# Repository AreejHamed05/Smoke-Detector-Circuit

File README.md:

# 🚨 Smoke/Gas Detector Circuit

A compact and affordable smoke/gas detection system using the **MQ-2 gas sensor**, designed for early fire warning. The system was built using **Proteus simulation**, **breadboard prototyping**, and **PCB implementation** for real-world testing.

---

## 🔧 Project Overview

This project detects flammable gases like smoke, methane, and LPG. When gas is detected above a threshold, the system triggers an **LED** and **buzzer** as a dual alert mechanism.

- 📦 Fully simulated using **Proteus** and **Tinkercad**
- ⚡ Implemented on both **breadboard** and **fabricated PCB**
- 🔋 Stable power regulation with **LM7805**

---

## 🧠 My Role

- Designed the full schematic and PCB layout using Proteus
- Simulated and debugged the circuit
- Assembled and calibrated the sensor and components on breadboard and PCB
- Performed real-world testing with and without gas exposure

---

## 🛠️ Tools & Components

- MQ-2 Gas Sensor
- LM7805 Voltage Regulator
- Buzzer, LED, Resistors
- Breadboard & PCB
- Proteus (Simulation)
- Tinkercad (Virtual circuit testing)

---

## ✅ Features

- Real-time gas detection
- Dual alert: visual (LED) and sound (buzzer)
- Compact PCB layout for physical implementation
- Safe and affordable system

---

## 📅 Date

**Fall 2024 – 2025** (University project)

---

## ✍️ Author

**Areej Abdelghany Hamed**  
Mechatronics Engineering Student  
[LinkedIn](https://www.linkedin.com/in/areejhamed) | areejhamed05@gmail.com

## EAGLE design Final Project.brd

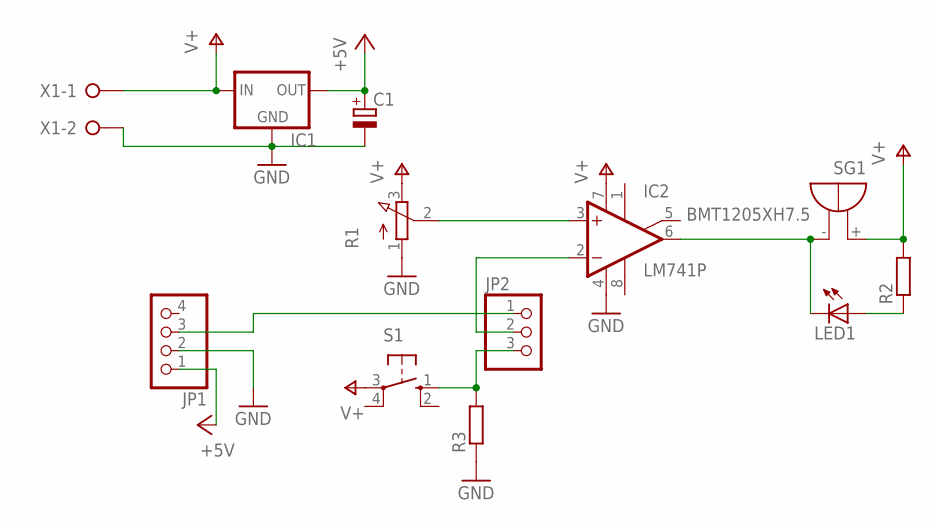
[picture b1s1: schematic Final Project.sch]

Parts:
C1: CPOL-EUE2.5-7; E2,5-7
IC1: 78MXXS
IC2: LM741P; DIL08
JP1: PINHD-1X4; 1X04
JP2: PINHD-1X3; 1X03
LED1: LED5MM
R1: 3RP/1610N
R2, R3: R-EU_0207/7; 0207/7
S1: 10-XX; B3F-10XX
SG1: BMT1205XH7.5
X1: W237-02P; W237-132

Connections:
+5V: C1.+, IC1.OUT, JP1.1
GND: C1.-, IC1.GND, IC2.4 (V-), JP1.2, R1.1 (A), R3.1, X1.2
unnamed: JP2.3, R3.2, S1.1 (S)
unnamed: JP1.3, JP2.1
unnamed: IC2.3 (+IN), R1.2 (S)
unnamed: IC2.6 (OUT), LED1.K (C), SG1.-
unnamed: LED1.A, R2.1
unnamed: IC2.2 (-IN), JP2.2
V+: IC1.IN, IC2.7 (V+), R1.3 (E), R2.2, S1.3, SG1.+, X1.1

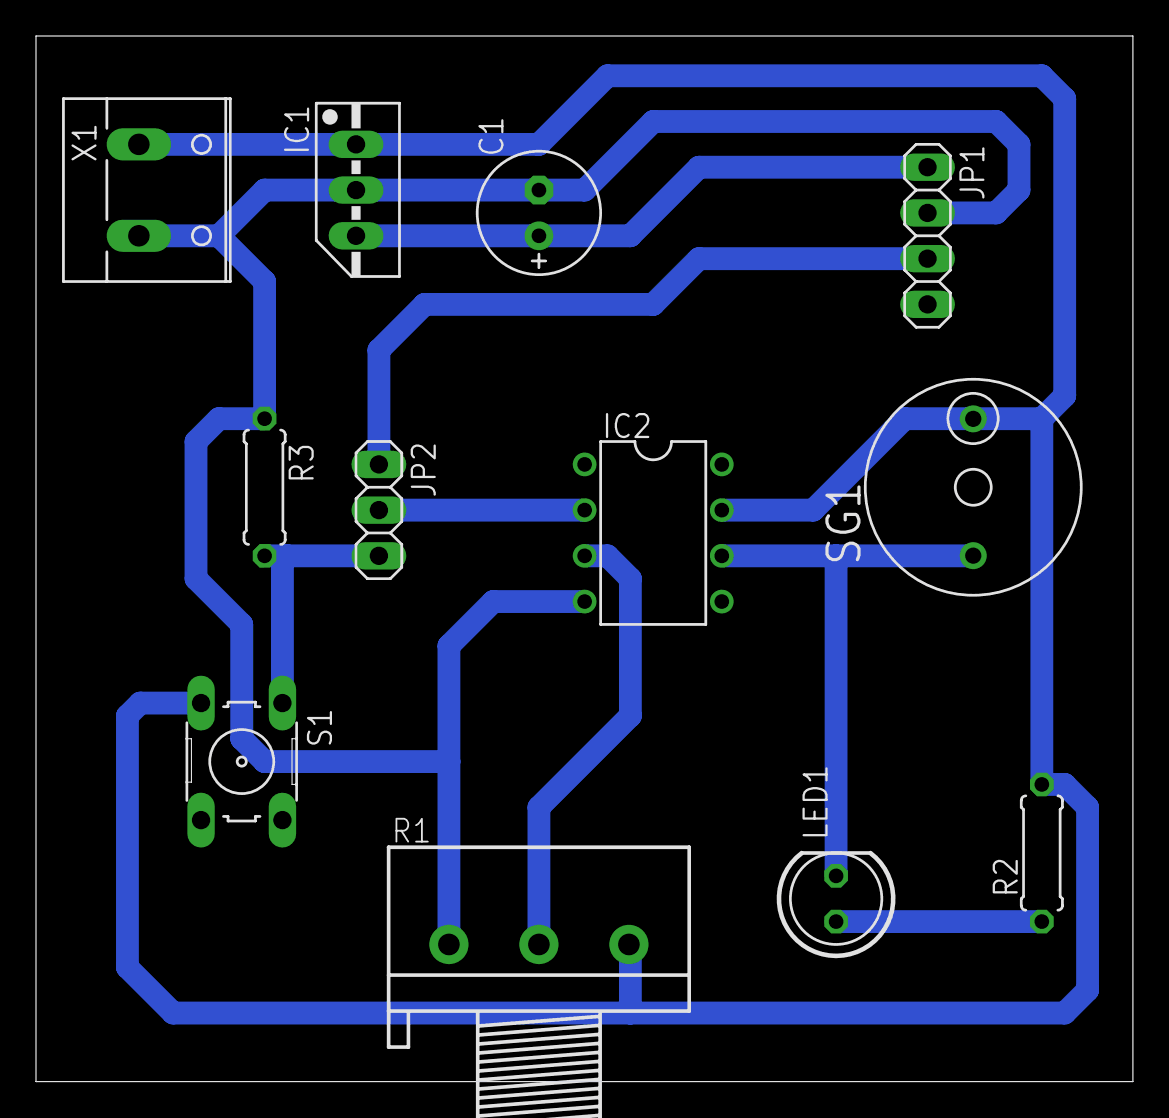
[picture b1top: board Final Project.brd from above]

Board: 2 copper layers, 60.9 x 58.1 mm, 12 parts (0 on the bottom side), 9 nets.
